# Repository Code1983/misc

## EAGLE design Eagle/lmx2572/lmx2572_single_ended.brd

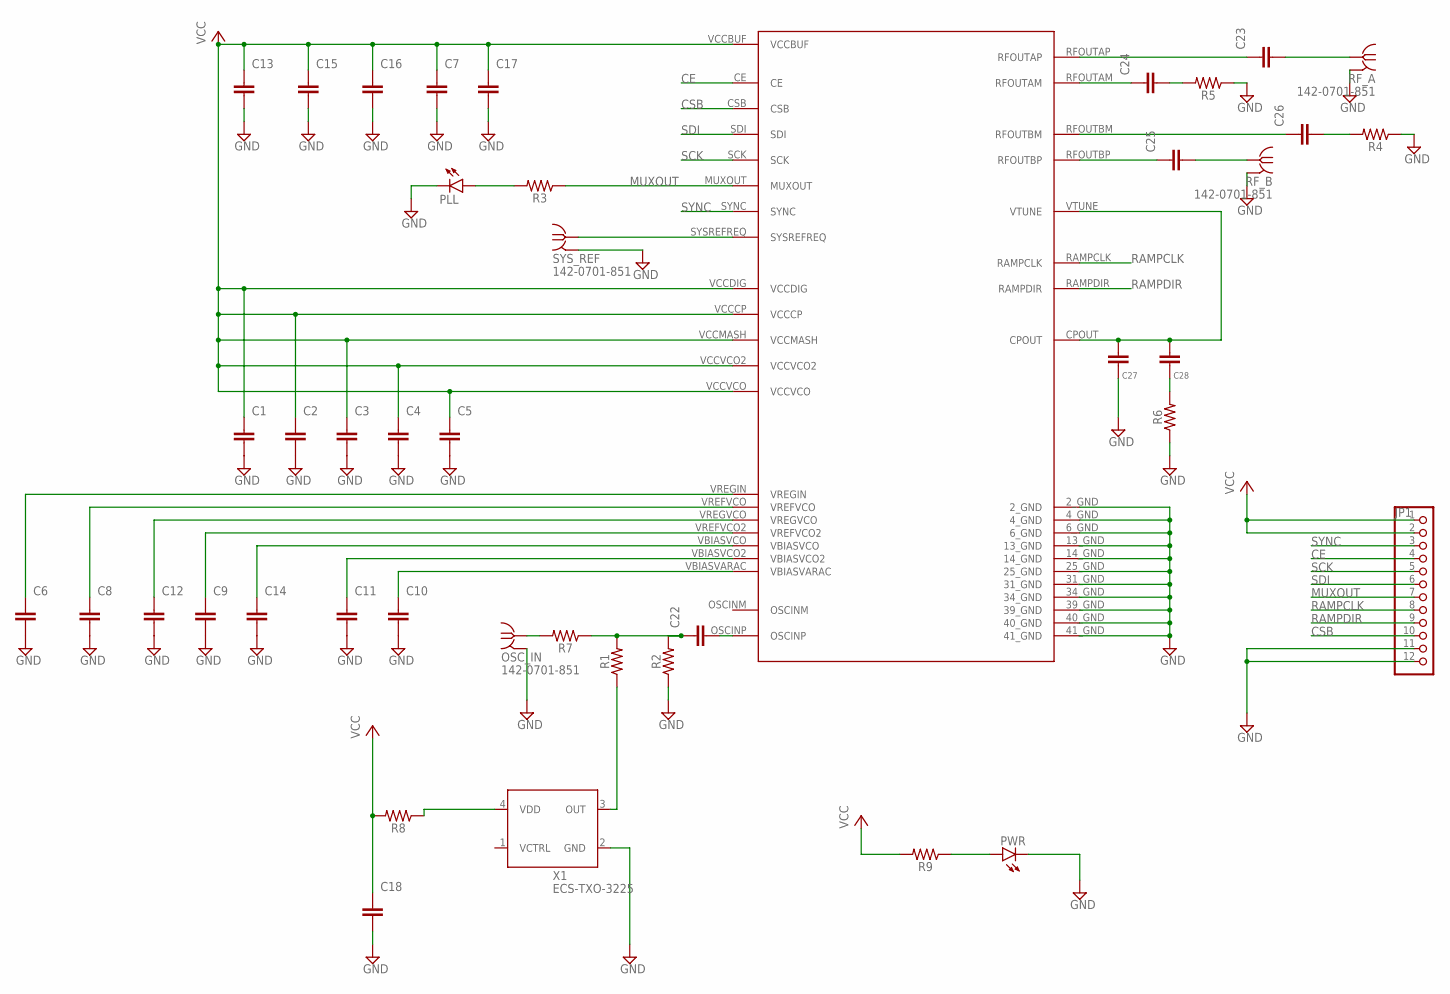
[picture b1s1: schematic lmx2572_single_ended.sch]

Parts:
C1, C2, C3, C4, C5, C6: 1.0uF; .0603-B-NOSILK
C7, C11, C13, C17: 0.1uF; .0603-B-NOSILK
C8, C9, C10, C15, C16, C18: 10uF; .0603-B-NOSILK
C12: 10nF; .0603-B-NOSILK
C14: 470pF; .0603-B-NOSILK
C22: 0.1uF; .0402-C-NOSILK
C23, C24, C25, C26: 100PF; .0402-C-NOSILK
C27: 4.7nf; .0402-C-NOSILK
C28: 220nf; .0402-C-NOSILK
JP1: PINHD-1X12; 1X12
OSC_IN: 142-0701-851
PLL: LEDCHIP-LED0603; CHIP-LED0603
PWR: LEDCHIP-LED0603; CHIP-LED0603
R1, R7, R8: 0; .0402-C-NOSILK
R2, R4, R5: 50; .0402-C-NOSILK
R3, R9: 330; .0603-B-NOSILK
R6: 100; .0402-C-NOSILK
RF_A: 142-0701-851
RF_B: 142-0701-851
SYS_REF: 142-0701-851
U$1: LMX2572_QFN
X1: ECS-TXO-3225; 3.2X2.5

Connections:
CE: JP1.4, U$1.CE
CSB: JP1.10, U$1.CSB
GND: C1.2, C2.2, C3.2, C4.2, C5.2, C6.2, C7.2, C8.2, C9.2, C10.2, C11.2, C12.2, C13.2, C14.2, C15.2, C16.2, C17.2, C18.2, C27.1, JP1.11, JP1.12, OSC_IN.GND1 (GND), OSC_IN.GND2 (GND), OSC_IN.GND3 (GND), OSC_IN.GND4 (GND), PLL.C, PWR.C, R2.1, R4.1, R5.1, R6.1, RF_A.GND1 (GND), RF_A.GND2 (GND), RF_A.GND3 (GND), RF_A.GND4 (GND), RF_B.GND1 (GND), RF_B.GND2 (GND), RF_B.GND3 (GND), RF_B.GND4 (GND), SYS_REF.GND1 (GND), SYS_REF.GND2 (GND), SYS_REF.GND3 (GND), SYS_REF.GND4 (GND), U$1.2_GND, U$1.4_GND, U$1.6_GND, U$1.13_GND, U$1.14_GND, U$1.25_GND, U$1.31_GND, U$1.34_GND, U$1.39_GND, U$1.40_GND, U$1.41_GND, X1.2 (GND)
MUXOUT: JP1.7, R3.1, U$1.MUXOUT
unnamed: C10.1, U$1.VBIASVARAC
unnamed: C11.1, U$1.VBIASVCO2
unnamed: C14.1, U$1.VBIASVCO
unnamed: C9.1, U$1.VREFVCO2
unnamed: C12.1, U$1.VREGVCO
unnamed: C8.1, U$1.VREFVCO
unnamed: C6.1, U$1.VREGIN
unnamed: C22.2, U$1.OSCINP
unnamed: R1.1, X1.3 (OUT)
unnamed: R8.1, X1.4 (VDD)
unnamed: OSC_IN.RF1 (RF), R7.2
unnamed: C28.1, R6.2
unnamed: SYS_REF.RF1 (RF), U$1.SYSREFREQ
unnamed: PLL.A, R3.2
unnamed: C26.1, U$1.RFOUTBM
unnamed: C23.1, U$1.RFOUTAP
unnamed: C23.2, RF_A.RF1 (RF)
unnamed: C25.2, RF_B.RF1 (RF)
unnamed: C25.1, U$1.RFOUTBP
unnamed: C24.1, U$1.RFOUTAM
unnamed: C22.1, R1.2, R2.2, R7.1
unnamed: C26.2, R4.2
unnamed: C24.2, R5.2
unnamed: C27.2, C28.2, U$1.CPOUT, U$1.VTUNE
unnamed: PWR.A, R9.1
RAMPCLK: JP1.8, U$1.RAMPCLK
RAMPDIR: JP1.9, U$1.RAMPDIR
SCK: JP1.5, U$1.SCK
SDI: JP1.6, U$1.SDI
SYNC: JP1.3, U$1.SYNC
VCC: C1.1, C2.1, C3.1, C4.1, C5.1, C7.1, C13.1, C15.1, C16.1, C17.1, C18.1, JP1.1, JP1.2, R8.2, R9.2, U$1.VCCBUF, U$1.VCCCP, U$1.VCCDIG, U$1.VCCMASH, U$1.VCCVCO, U$1.VCCVCO2

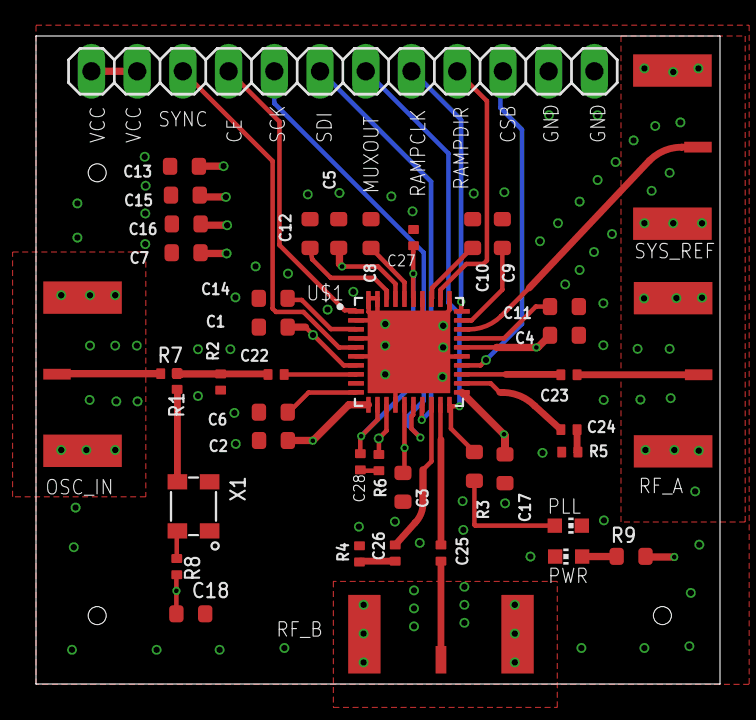
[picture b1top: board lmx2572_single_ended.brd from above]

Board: 4 copper layers, 38.0 x 36.0 mm, 43 parts (0 on the bottom side), 35 nets.

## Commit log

2018-07-29 Comaprison of pytorch, numpy, tensorflow, numba matrix capabilities
2019-12-26 Eagle files added.
2019-12-27 removed unused files
2019-12-27 update eagle file
2019-12-29 added TCXO
2019-12-30 more vias
2019-12-30 added text
2019-12-30 text on correct layer
2019-12-30 removed thermal clearance.
2019-12-31 review and updates before sending it to oshpark
2020-01-21 added chibios submodule and LMX2572 synth code
2020-01-23 loop trough various config for mx2572
